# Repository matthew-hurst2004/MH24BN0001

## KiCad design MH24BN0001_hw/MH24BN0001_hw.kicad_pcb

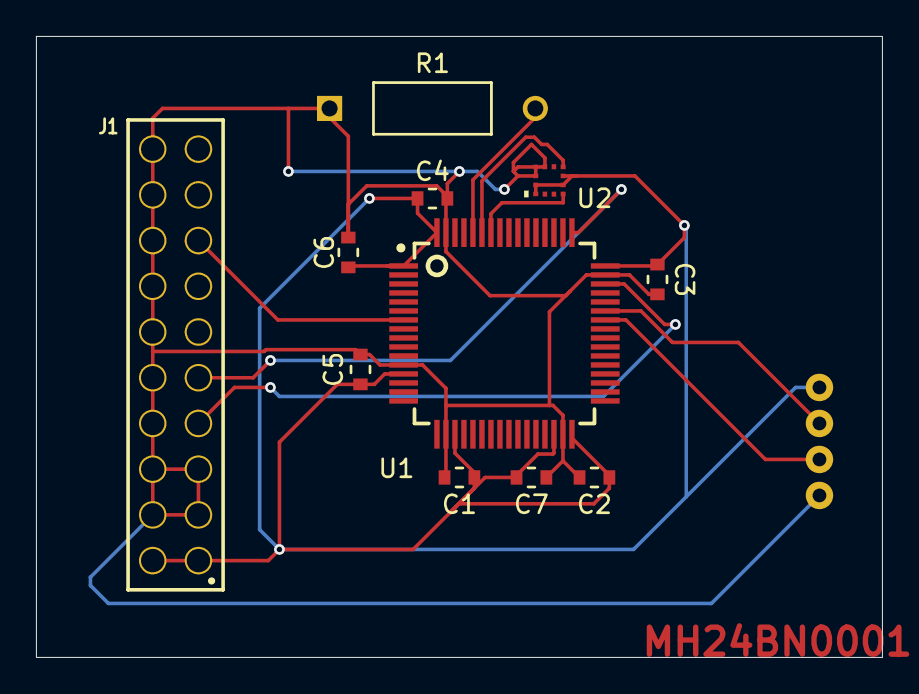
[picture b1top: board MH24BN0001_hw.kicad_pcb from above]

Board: 2 copper layers, 47.0 x 34.5 mm, 12 parts (0 on the bottom side), 10 nets.

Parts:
C1, C2, C3, C4, C5, C6: 1µF; 1µF_cap
C7: 2.2µF; 2.2µF_cap
J1: ST-Link V2 Header; 61302021821
R1: 10 kΩ
SI1: serial_interface
U1: STM32F401RBT6; QFP50P1200X1200X160-64N
U2: Accelerometer; acc

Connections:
+3.3V: C1.1, C2.1, C3.1, C4.1, C5.1, C6.1, C7.1, J1.1, J1.2, SI1.1 (VCC), U1.1 (VBAT), U1.13 (VREF+), U1.19 (VDD), U1.30 (VCAP1), U1.32 (VDD__1), U1.48 (VDD__2), U1.64 (VDD__3), U2.2 (CS), U2.3 (SDO/SA0), U2.9 (VDD), U2.10 (VDDIO)
/MCU_RX: SI1.2 (TX), U1.43 (PA10)
/MCU_TX: SI1.3 (RX), U1.42 (PA9)
/NRST: J1.15, U1.7 (NRST)
/SCL: U1.58 (PB6), U2.1 (SCL/SPC)
/SDA: U1.59 (PB7), U2.4 (SDA/SDI/SDO)
/SWCLK: J1.9, U1.49 (PA14)
/SWDIO: J1.7, U1.46 (PA13)
GND: C1.2, C2.2, C3.2, C4.2, C5.2, C6.2, C7.2, J1.3, J1.4, J1.5, J1.6, J1.8, J1.10, J1.12, J1.14, J1.16, J1.18, J1.20, R1.1, SI1.4 (GND), U1.12 (VREF-), U1.18 (VSS), U1.31 (VSS__1), U1.47 (VSS__2), U1.63 (VSS__3), U2.6 (GND), U2.7 (RES), U2.8 (GND)
unnamed: R1.2, U1.60 (BOOT0)

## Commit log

2024-11-20 Adding sub-directory for hardware files
2024-11-20 Removing all files
2024-11-20 Removing files again
2024-11-20 Adding final sub-directory for hardware files
2024-11-20 Adding footprint and symbol libraries, creating symbol for STM32, importing footprint for header, placing header and doing simple wiring, placing STM32 with no wiring
2024-11-20 Adding datasheet to chip
2024-11-20 previous commit
2024-11-21 Changing chip to STM32F401RB
2024-11-21 Adding essential pin functions to STM32F4
2024-11-21 Adding SWDIO and SWCLK
2024-11-21 Adding serial interface to board, finishing schematic
2024-11-22 starting PCB
2024-11-24 finishing pcb, generating output files
2024-11-24 Adding datasheet for STlink header
2024-11-25 Generating new and final output files by which I ordered the PCB
